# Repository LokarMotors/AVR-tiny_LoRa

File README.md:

# AVR-tiny_LoRa
# LoRaWAN node based on ATTiny87/167 and RFM95 #

Small LoRaWAN node with a temperature, air pressure and soil moisture sensor. Code includes modified Adafruit BMP180, LoRaWAN, RFM95 and custom Cayenne libraries to save flash. Circuit in made in EAGLE and includes a few avr circuit design considerations. ATTiny chip is programmed via ISP pins. Measured current consumption in deep sleep is 5μA at 3.3V and drops down to 3.9μA at 1.8V. Wake current consumption is 96.4mA at 3.3V and 79.5mA at 1.8V. Because of the RFM95 transmitter the maximum voltage is capped at 3.7V and the system is supplied with two AA batteries. According to simulations i made in Matlab the system could for 8 years in normal temperature conditions and uplinks every 30min. If there is a possibility to switch the RFM95 for a transmitter that is 5V tolerant the life expectancy of the device would be around 12 years with the same conditions with three AA batteries. Battery life is also affected by the spreading factor, table below shows wake time and battery life vs spreading factor.  

## Spread factor table (125k bandwith)

| Spreading factor  | Wake time | Battery life |
| ------------- | ------------- | ------------- |
| SF7 | 61 ms | 8.9 years |
| SF8 | 61 ms | 8.9 years |
| SF9 | 208 ms | 8.6 years |
| SF10 | 411 ms | 7.8 years |
| SF11 | 823 ms | 6.2 years |
| SF12 | 1483 ms | 4.2 years |

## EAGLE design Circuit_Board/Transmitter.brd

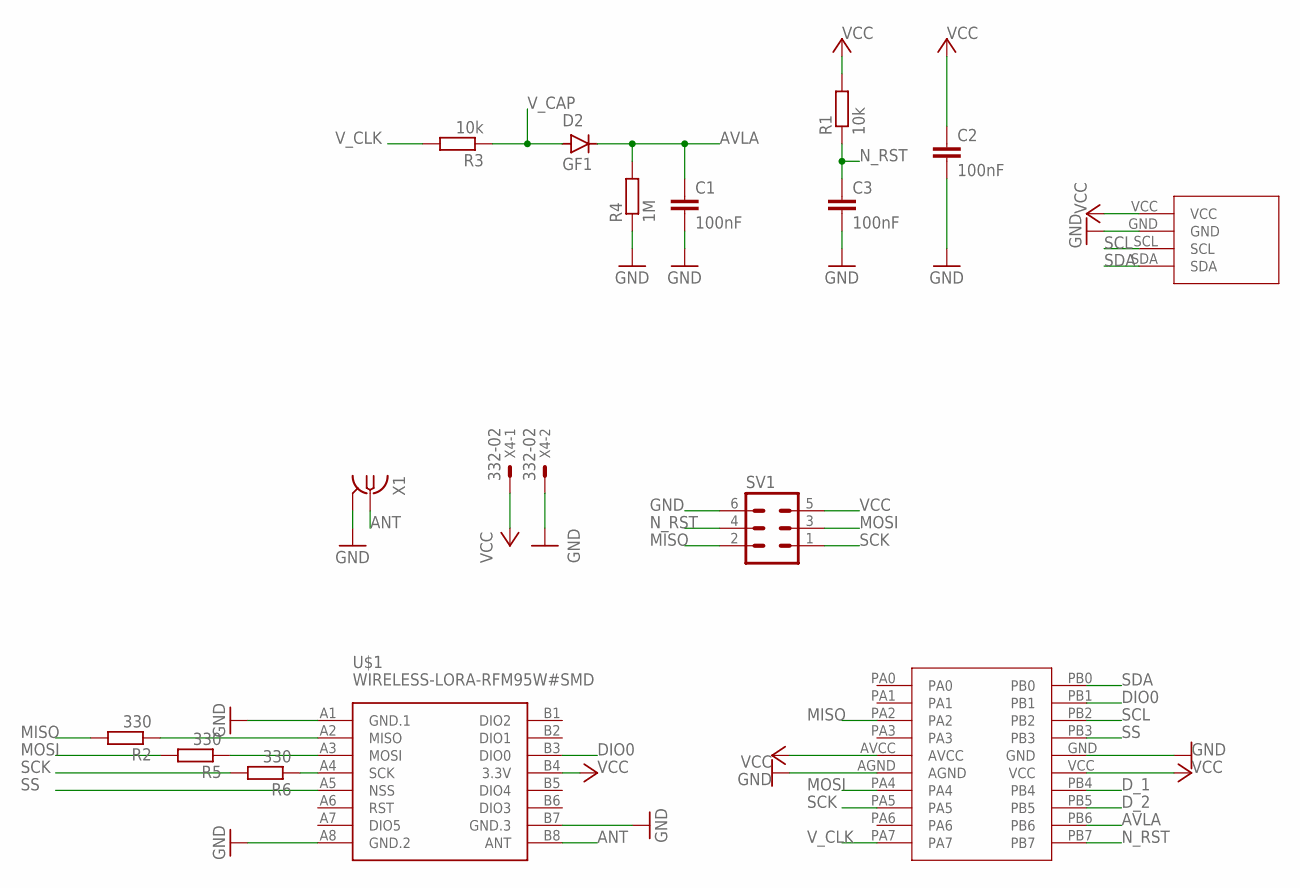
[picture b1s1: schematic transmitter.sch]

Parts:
ATTINY87_1: ATTINY87_SOIC; 20-SOIC
C1, C2, C3: 100nF; C1206
D2: GF1; SMA-DO214AC
GY-68-1: GY-68-4
R1, R3: 10k; R0805
R2, R5, R6: 330; R0805
R4: 1M; R0805
SV1: MA03-2
U$1: WIRELESS-LORA-RFM95W#SMD
X1: BU-SMA-G
X4: 332-02

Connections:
ANT: U$1.B8 (ANT), X1.1
AVLA: ATTINY87_1.PB6, C1.1, D2.K (C), R4.2
DIO0: ATTINY87_1.PB1, U$1.B3 (DIO0)
D_1: ATTINY87_1.PB4
D_2: ATTINY87_1.PB5
GND: ATTINY87_1.AGND, ATTINY87_1.GND, C1.2, C2.2, C3.2, GY-68-1.GND, R4.1, SV1.6, U$1.A1 (GND.1), U$1.A8 (GND.2), U$1.B7 (GND.3), X1.2, X1.3 (2), X1.4 (2), X1.5 (2), X4.2
MISO: ATTINY87_1.PA2, R2.2, SV1.2
MOSI: ATTINY87_1.PA4, R5.2, SV1.3
unnamed: R2.1, U$1.A2 (MISO)
unnamed: R5.1, U$1.A3 (MOSI)
unnamed: R6.1, U$1.A4 (SCK)
N_RST: ATTINY87_1.PB7, C3.1, R1.1, SV1.4
SCK: ATTINY87_1.PA5, R6.2, SV1.1
SCL: ATTINY87_1.PB2, GY-68-1.SCL
SDA: ATTINY87_1.PB0, GY-68-1.SDA
SS: ATTINY87_1.PB3, U$1.A5 (NSS)
VCC: ATTINY87_1.AVCC, ATTINY87_1.VCC, C2.1, GY-68-1.VCC, R1.2, SV1.5, U$1.B4 (3.3V), X4.1
V_CAP: D2.A, R3.1
V_CLK: ATTINY87_1.PA7, R3.2

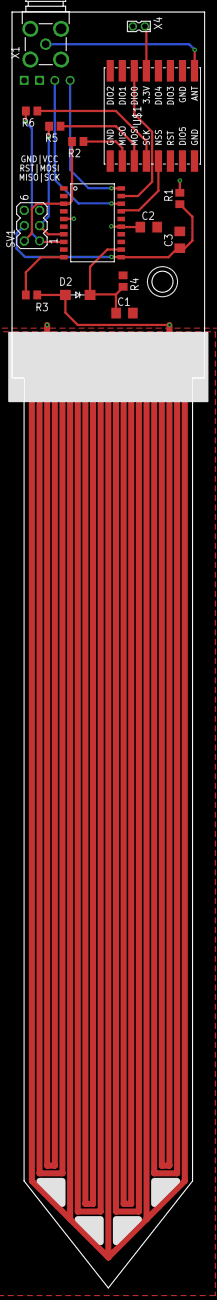
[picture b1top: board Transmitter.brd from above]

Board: 2 copper layers, 32.0 x 212.0 mm, 16 parts (1 on the bottom side), 17 nets.

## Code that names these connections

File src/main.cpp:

#include <Arduino.h>
#include <avr/sleep.h>
#include <avr/wdt.h>
#include <avr/io.h>
//#include <avr/interrupt.h>
#include <LoRaWAN.h>
#include <CAY_DIY.h>
#include <Adafruit_BMP085.h>
#include "config.h"
//#include <BMP180.h>

#define BUFF_LEN 100

// RFM95 pins
#define DIO0 9
#define NSS 11

#define SLEEP_TIME 190 // ~9.5s per cycle 190 ----> 30min

// SOIL MOISTURE pins
#define V_CLK 7 // CLOCK pin
#define AVLA 14 // ANALOG pin ADC9

// SOIL MOISTURE SENSOR SETTINGS:
#define MOIST_W 179 // WET
#define MOIST_D 222 // DRY
#define MAX_3V3 228 // MAX ANALOG VALUE AT 3.3 volts

#ifndef cbi
#define cbi(sfr, bit) (_SFR_BYTE(sfr) &= ~_BV(bit))
#endif
#ifndef sbi
#define sbi(sfr, bit) (_SFR_BYTE(sfr) |= _BV(bit))
#endif

RFM95 rfm(DIO0, NSS);
LoRaWAN lora = LoRaWAN(rfm);
uint16_t Frame_Counter_Tx = 0x0000;

// Global Variable to Track Deep Sleep
volatile uint16_t sleep_count = SLEEP_TIME;

// Custom CAYENNE library
CAYDIY cayenne(3);

// Modified Adafruit BMP180 library
Adafruit_BMP085 sensor;
int16_t dry, wet;

void goToSleep();
int16_t GetMoisture();

void setup()
{
  lora.setKeys(NwkSkey, AppSkey, DevAddr);
  rfm.init();
}

void loop()
{
  if (sleep_count >= SLEEP_TIME)
  {
    ADCSRA |= (1 << ADEN);
    pinMode(V_CLK, OUTPUT);
    digitalWrite(V_CLK, LOW); // discharging soil moisture capacitor
    if (sensor.begin(BMP085_ULTRALOWPOWER))
    {
      cayenne.Index = 0;
      cayenne.Add(0x01, 0x73, sensor.readPressure() / 10);

      int32_t X1 = (sensor.readRawTemperature() - (int32_t)sensor.ac6) * (int32_t)sensor.ac5 >> 15;
      int32_t X2 = ((int32_t)sensor.mc << 11) / (X1 + (int32_t)sensor.md);
      cayenne.Add(0x02, 0x67, (((X1 + X2 + 8) >> 4)));
      cayenne.Add(0x03, 0x02, map(GetMoisture(), MOIST_D, MOIST_W, 0, 10000));
    }

    lora.Send_Data(cayenne.Buffer, cayenne.Index, ++Frame_Counter_Tx);
    sleep_count = 0;
  }
  goToSleep();
}

void goToSleep()
{
  // Disable ADC, saves ~230uA
  ADCSRA &= ~(1 << ADEN);

  // setup watchdog "9" -> 8 sec
  MCUSR &= ~(1 << WDRF);
  WDTCR |= (1 << WDCE) | (1 << WDE);
  WDTCR = (9 & 7) | (1 << 5) | (1 << WDCE);
  WDTCR |= _BV(WDIE);
  ///////////////////////////////////

  set_sleep_mode(SLEEP_MODE_PWR_DOWN);
  sleep_mode();
  wdt_disable();
}

ISR(WDT_vect)
{
  sleep_count++; // keep track of how many sleep cycles have been completed.
}

int16_t GetMoisture()
{
  ADMUX &= 0b11000000; // clear last six bits
  ADMUX |= 0b00101001; // ADC9 and left adjust resaults for only 8-bit reading

  for (uint8_t i = 0; i < 255; i++)
  {
    delayMicroseconds(1);
    digitalWrite(V_CLK, HIGH);
    delayMicroseconds(1);
    digitalWrite(V_CLK, LOW);
  }
  ADCSRA |= (1 << ADSC); // start conversion
  while (!(ADCSRA & 1 << ADIF))
    ;
  int16_t out = (int16_t)ADCH;

  // compensation for battery discharge
  digitalWrite(V_CLK, HIGH);
  delay(15);
  ADCSRA |= (1 << ADSC);
  while (!(ADCSRA & 1 << ADIF))
    ;
  out += (int16_t)(MAX_3V3 - ADCH);
  digitalWrite(V_CLK, LOW);
  /////////////////////////////////////

  return out;
}

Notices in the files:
parts and their libraries:
diy-modules: Released under the Creative Commons Attribution 4.0 International License: http://creativecommons.org/licenses/by/4.0
